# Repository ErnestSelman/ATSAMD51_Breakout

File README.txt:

Notes:
-Board Dimentions: 61.180 mm x 30.365 mm
-Drill sizes were chosen to be one of your free sizes, if any of them is not exactly one of the free sizes then it can be changed to nearest free size.
-PTH Holes sizes are finish hole sizes.

-Drill files:
	-drill_npth.xln
	-dril_pth.xln
-Gerber files included:
	-copper_bottom.gbr
	-copper_top.gbr
	-profile.gbr
	-silkscreen_top.gbr
	-soldermask_bottom.gbr
	-soldermask_top.gbr
-Aditional Files:
	-gerber_job.gbrjob
	-README.txt
	-SAMD51_Breakout.brd
	-SAMD51_Breakout.sch

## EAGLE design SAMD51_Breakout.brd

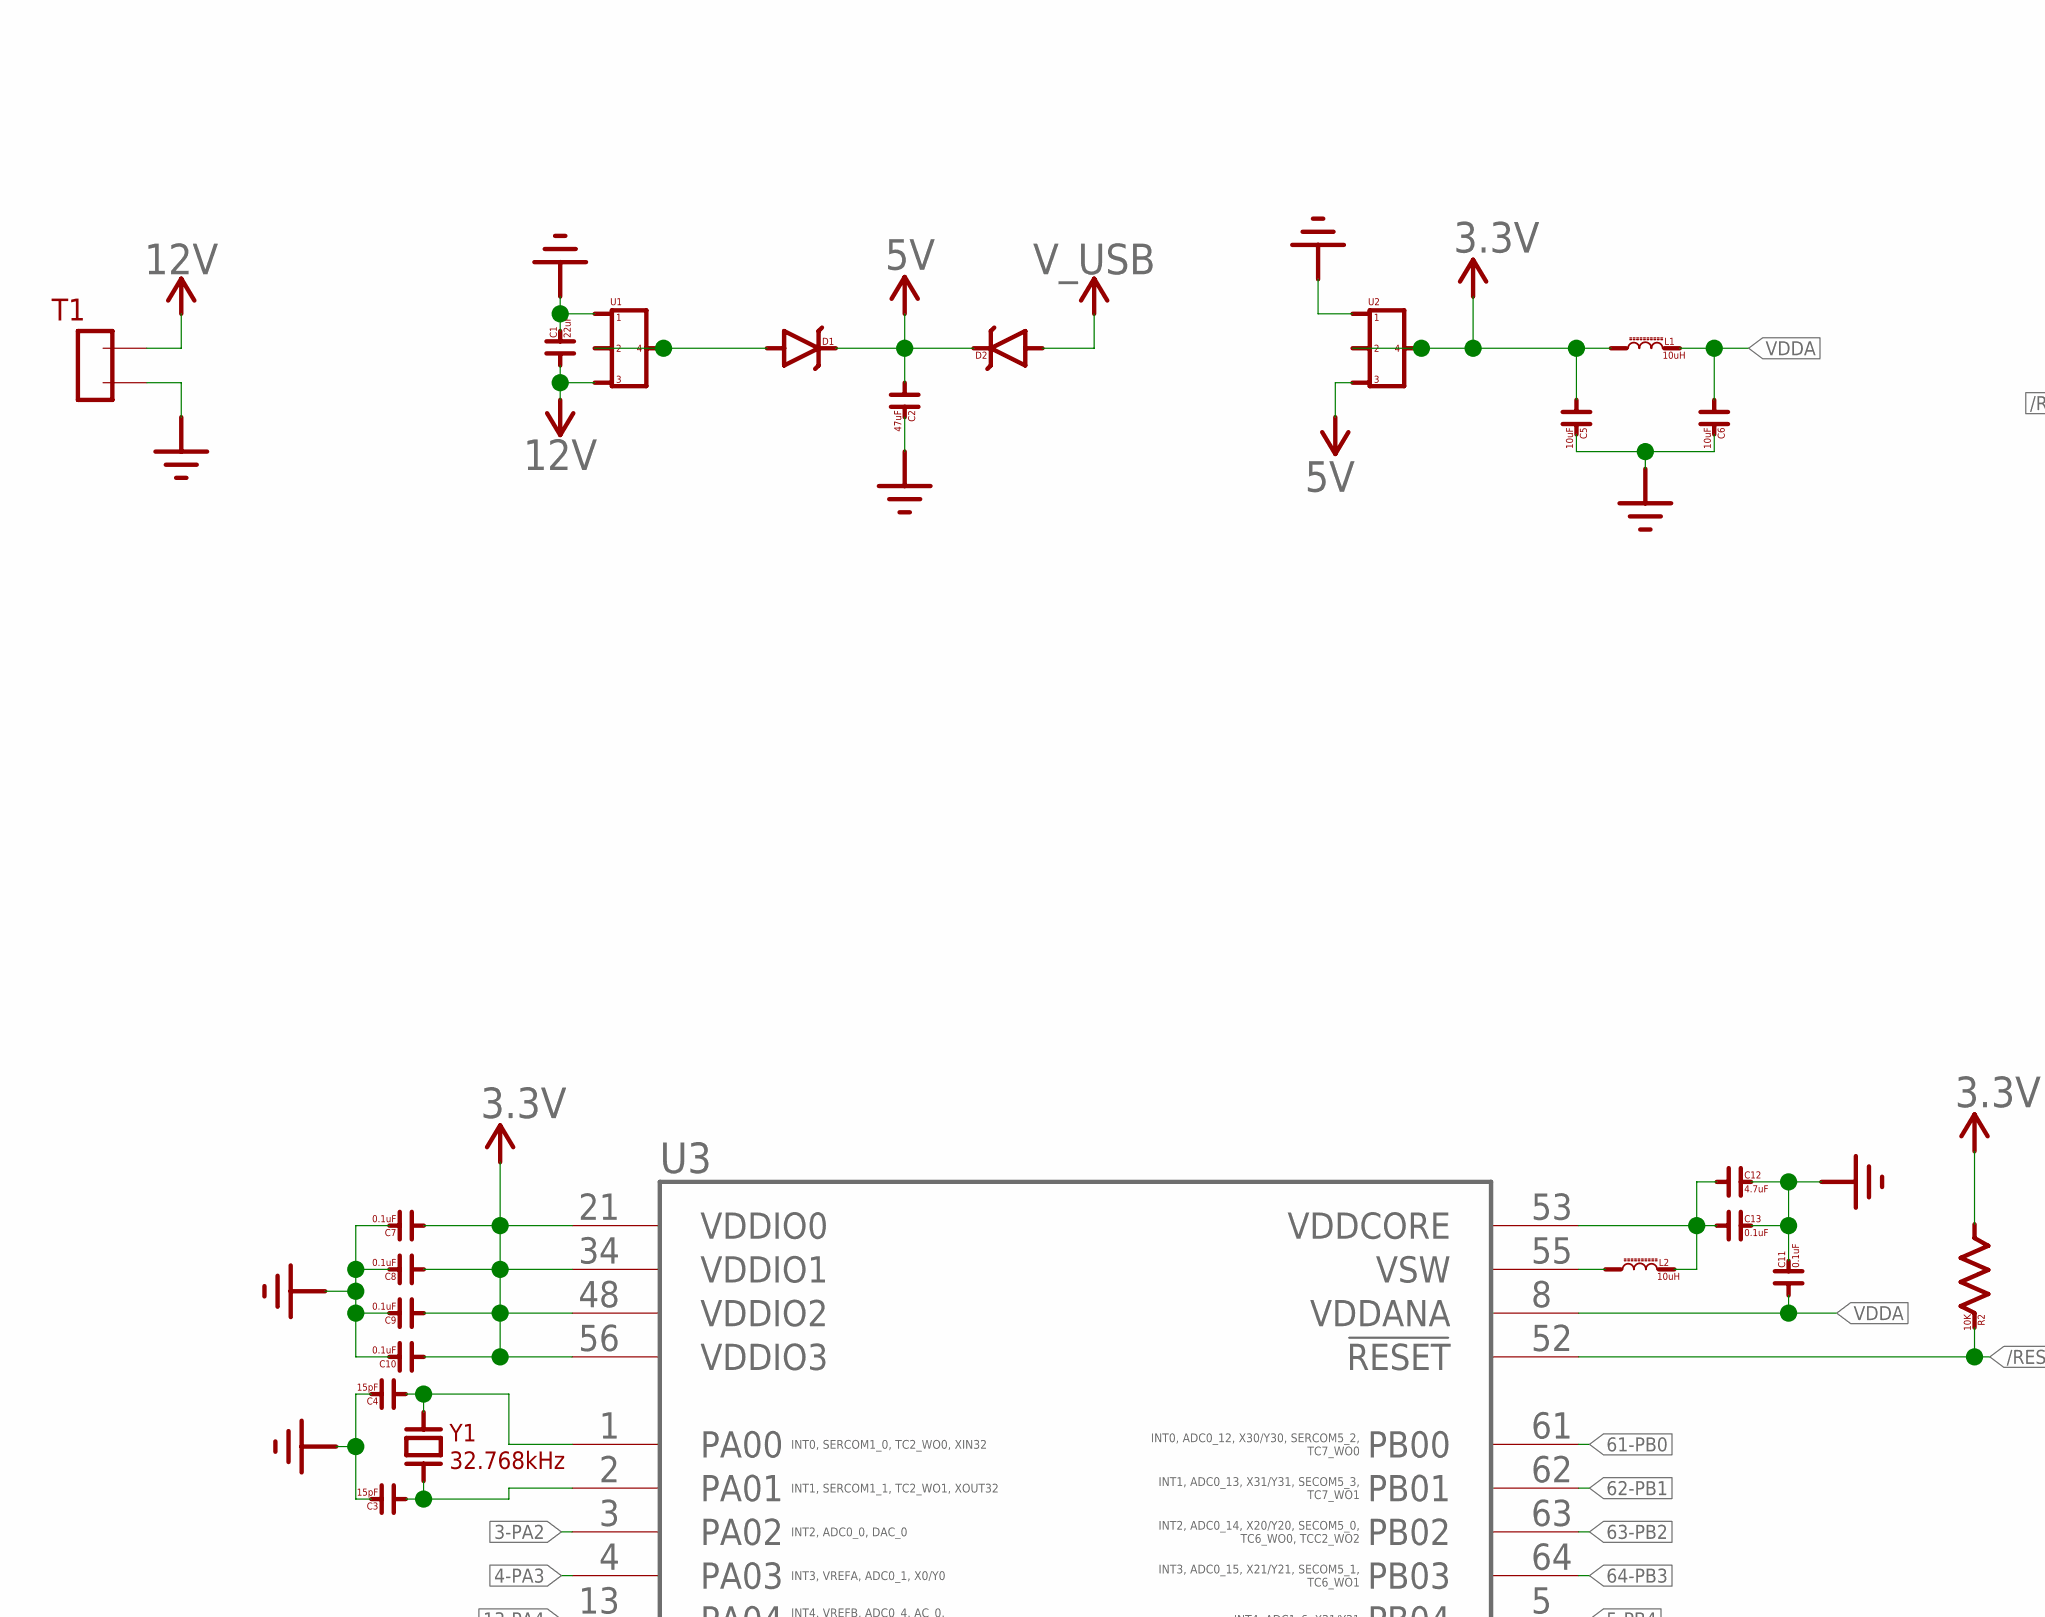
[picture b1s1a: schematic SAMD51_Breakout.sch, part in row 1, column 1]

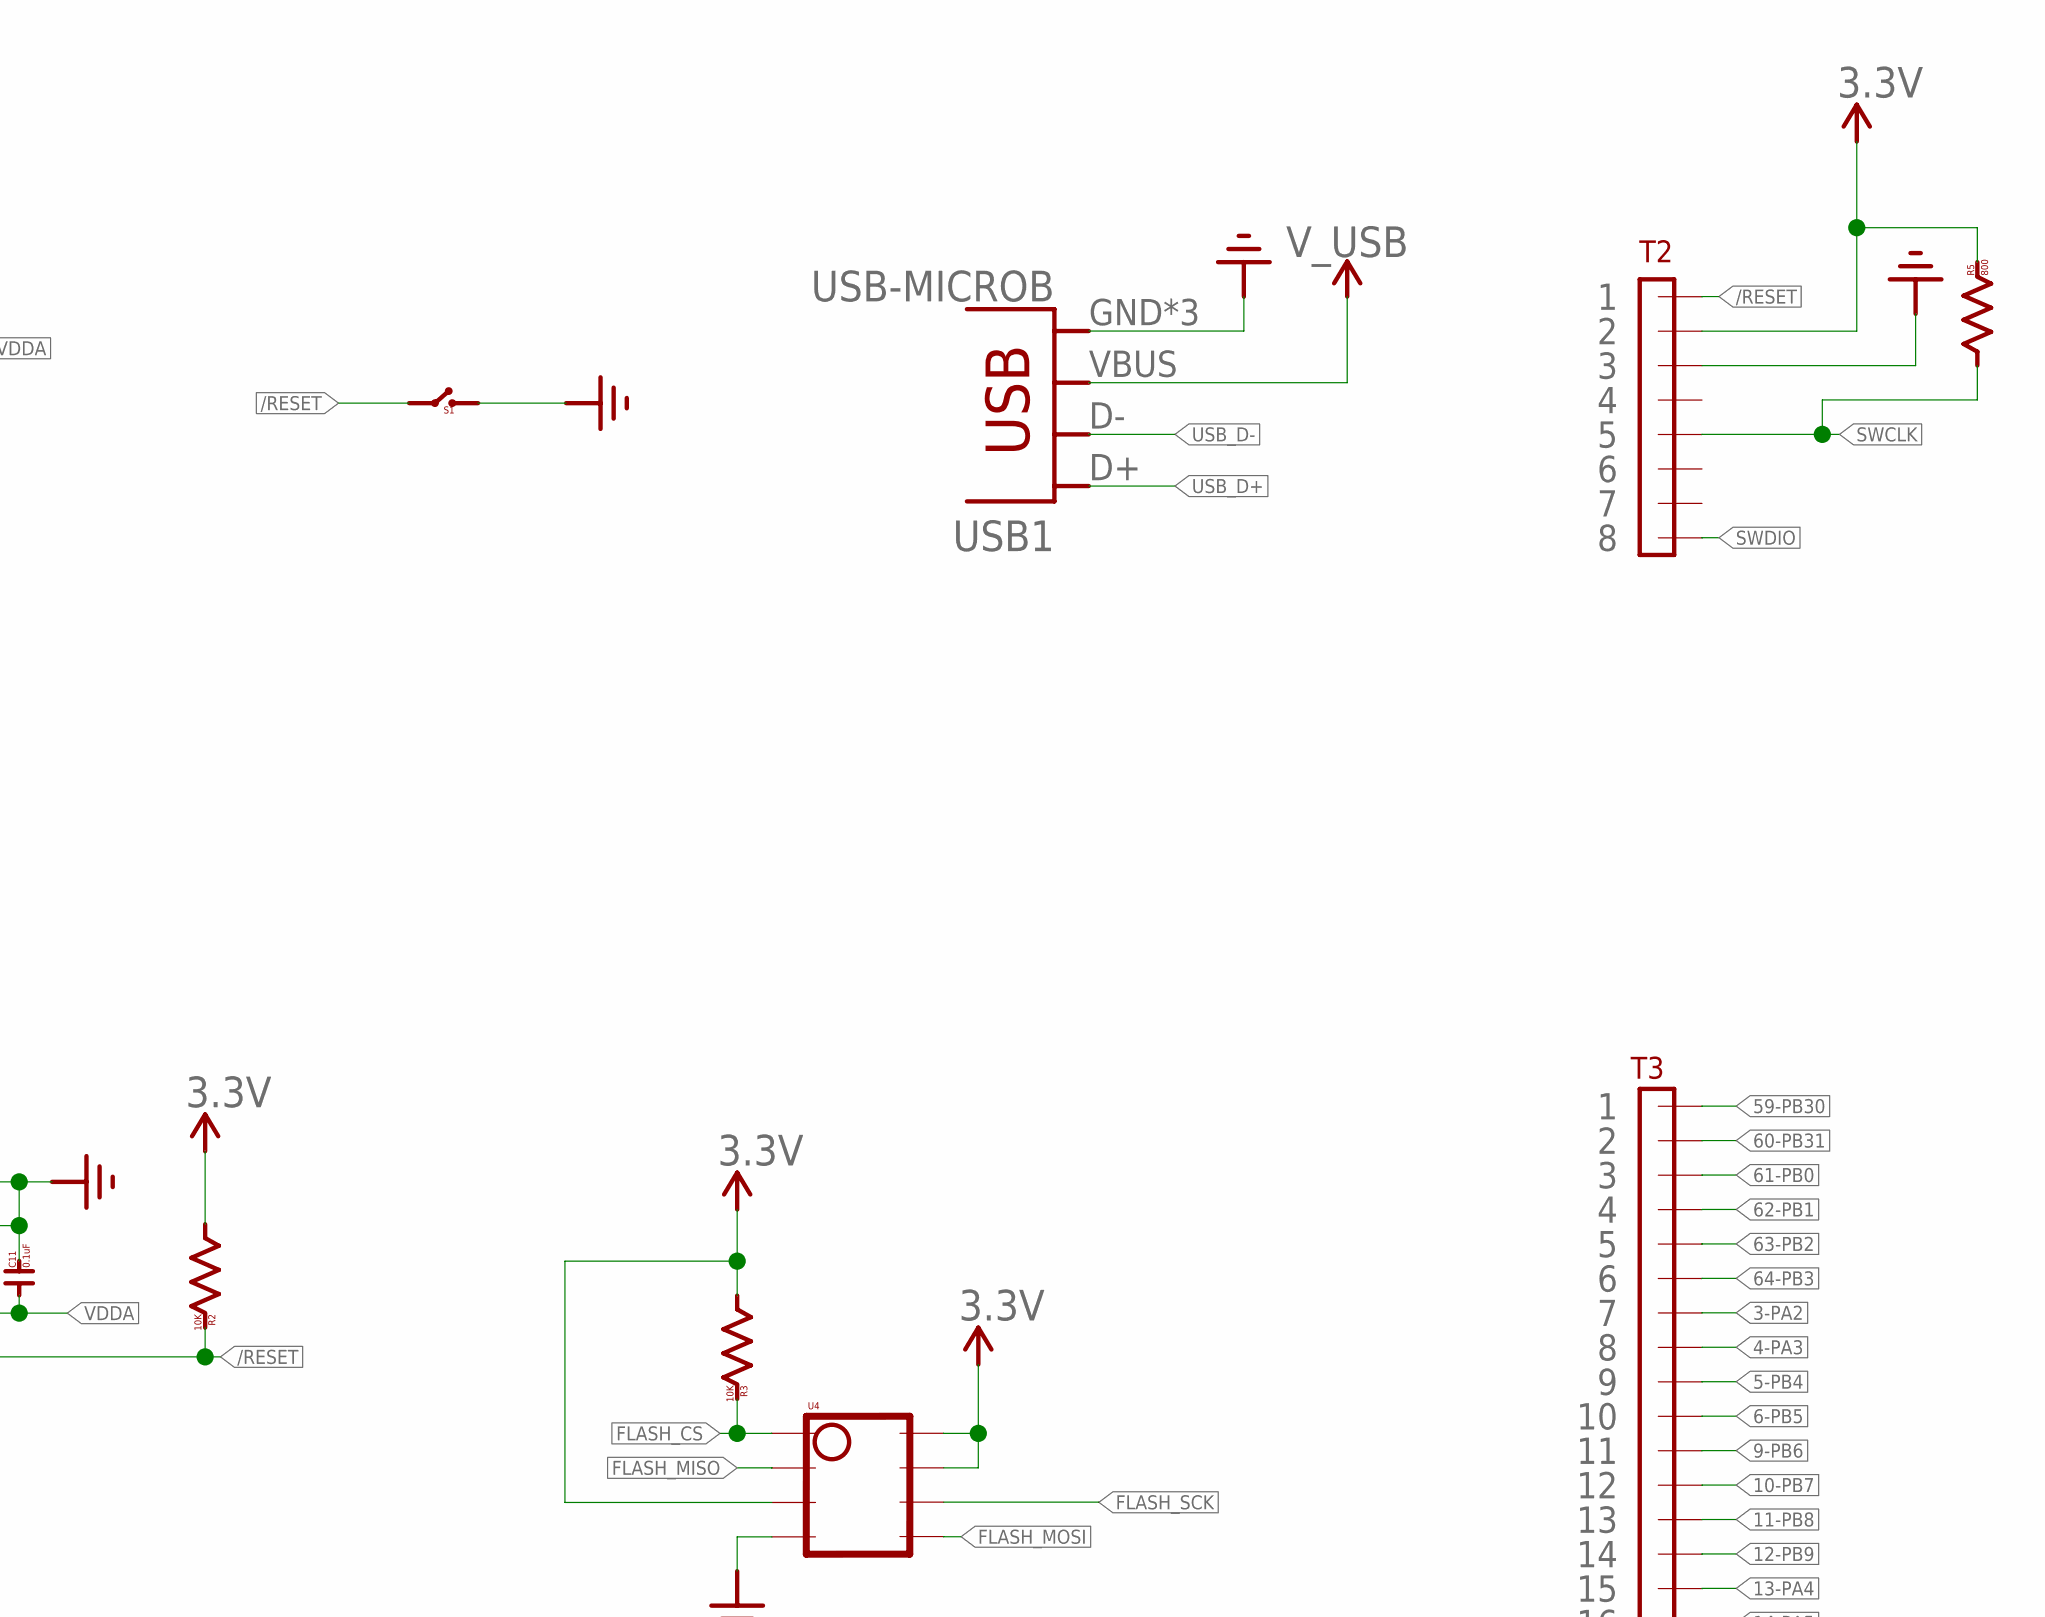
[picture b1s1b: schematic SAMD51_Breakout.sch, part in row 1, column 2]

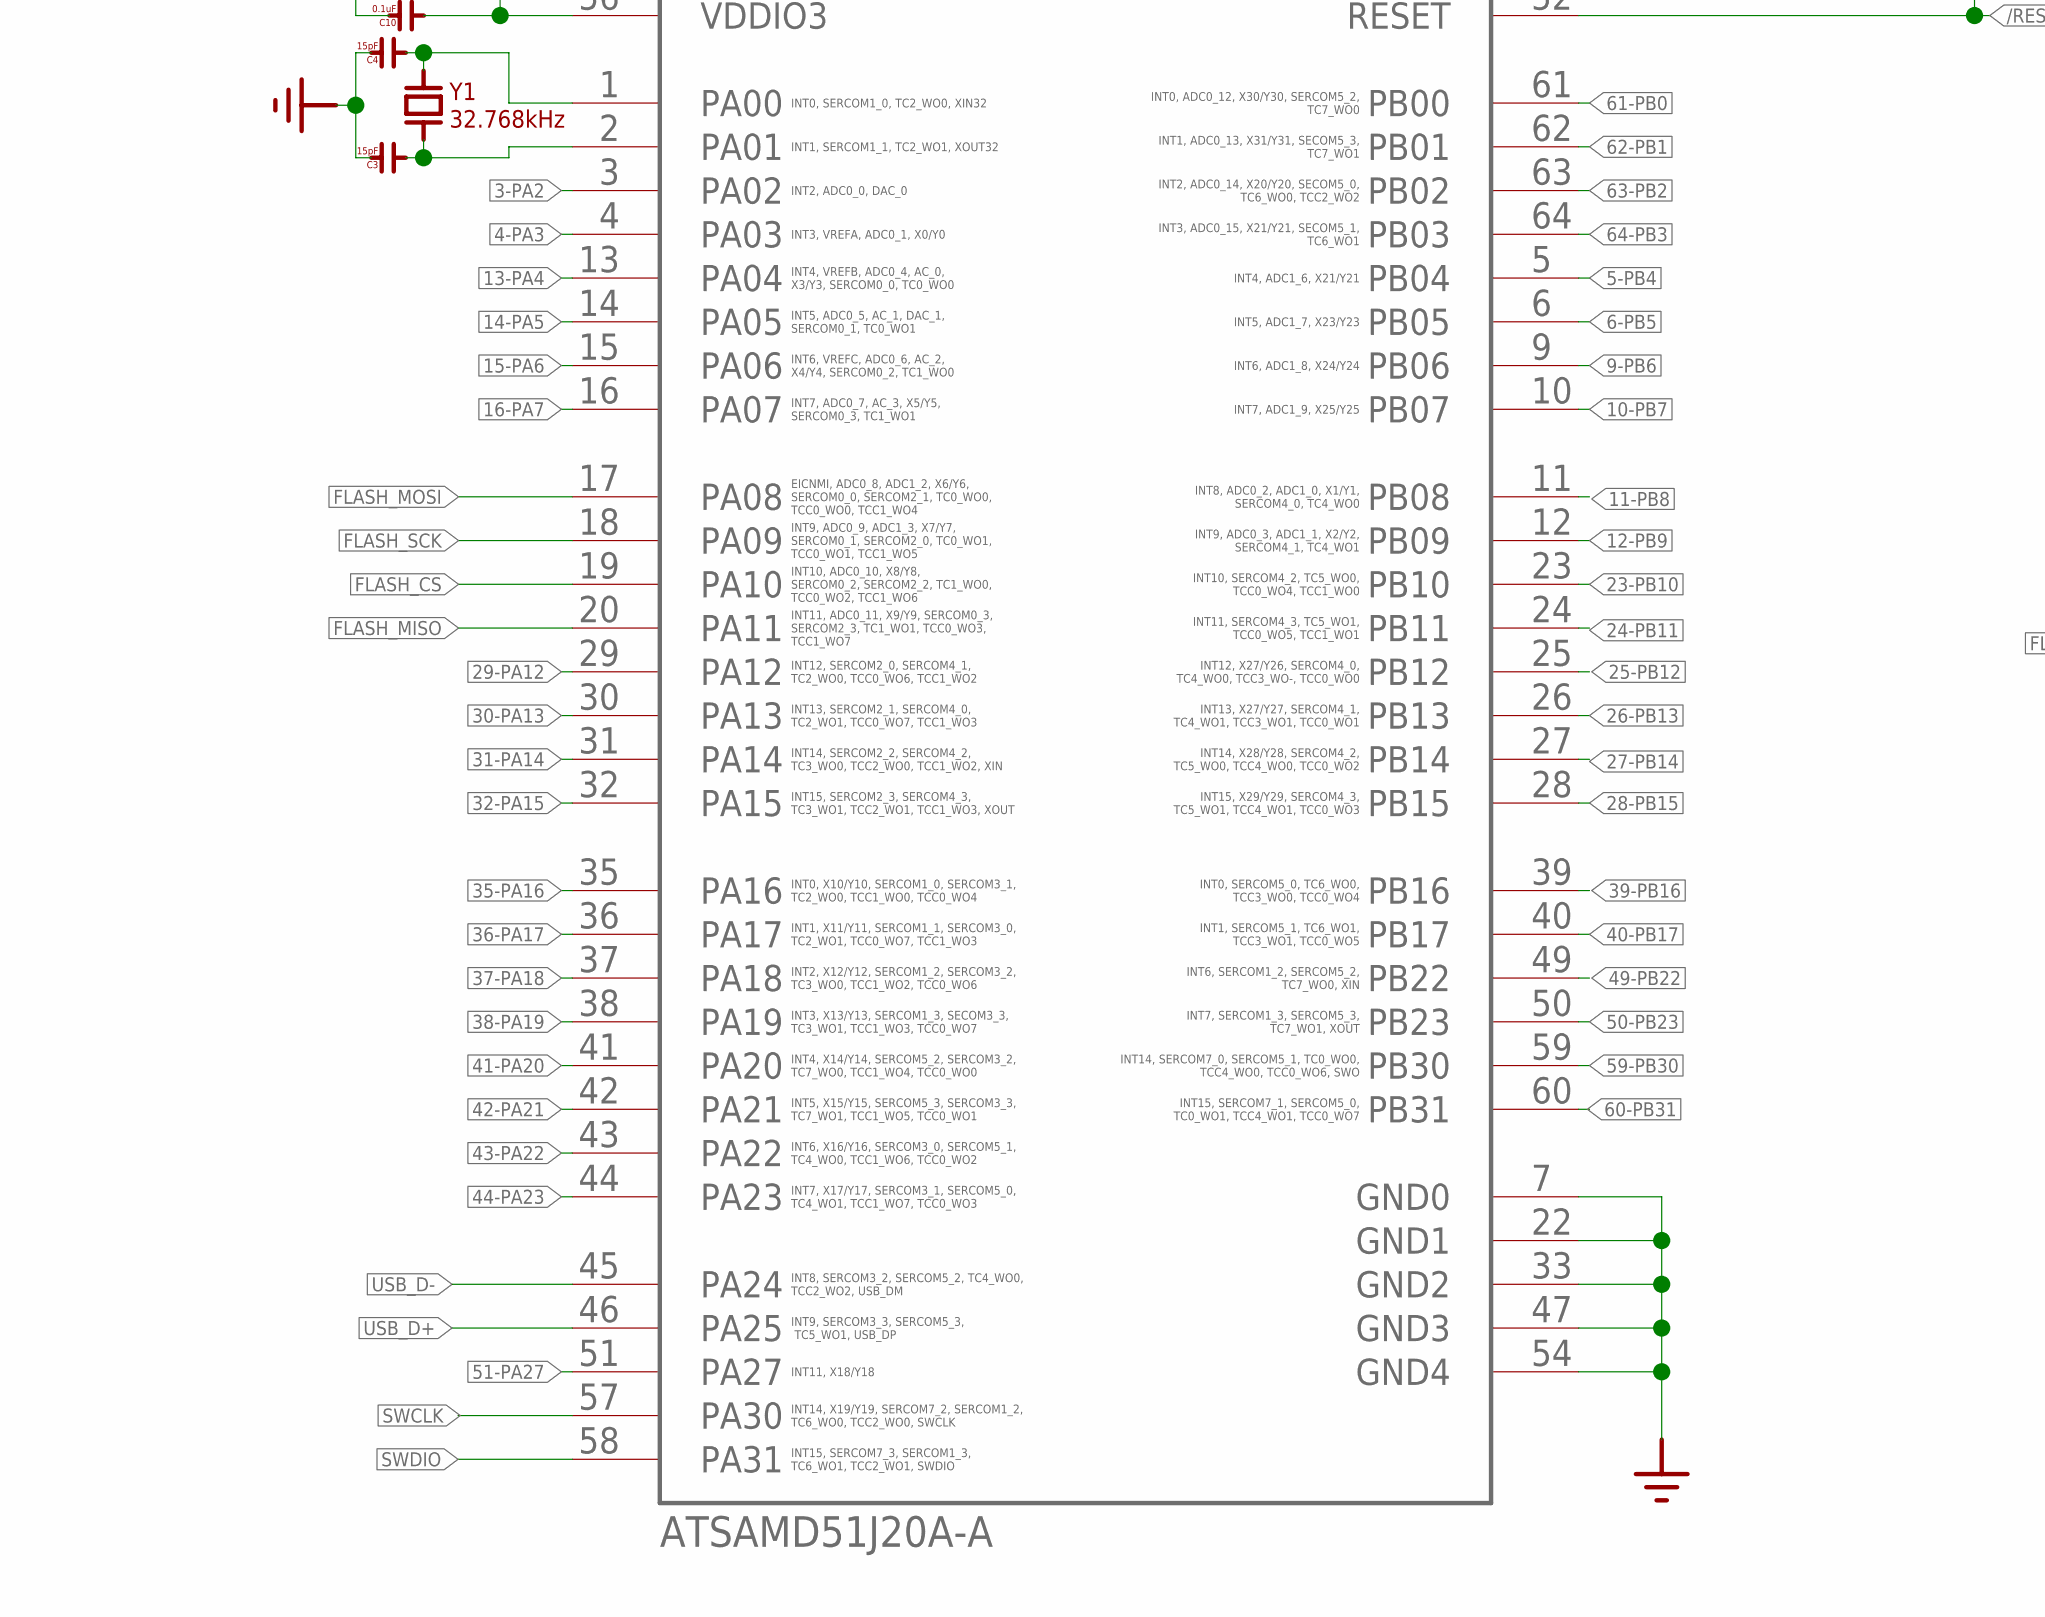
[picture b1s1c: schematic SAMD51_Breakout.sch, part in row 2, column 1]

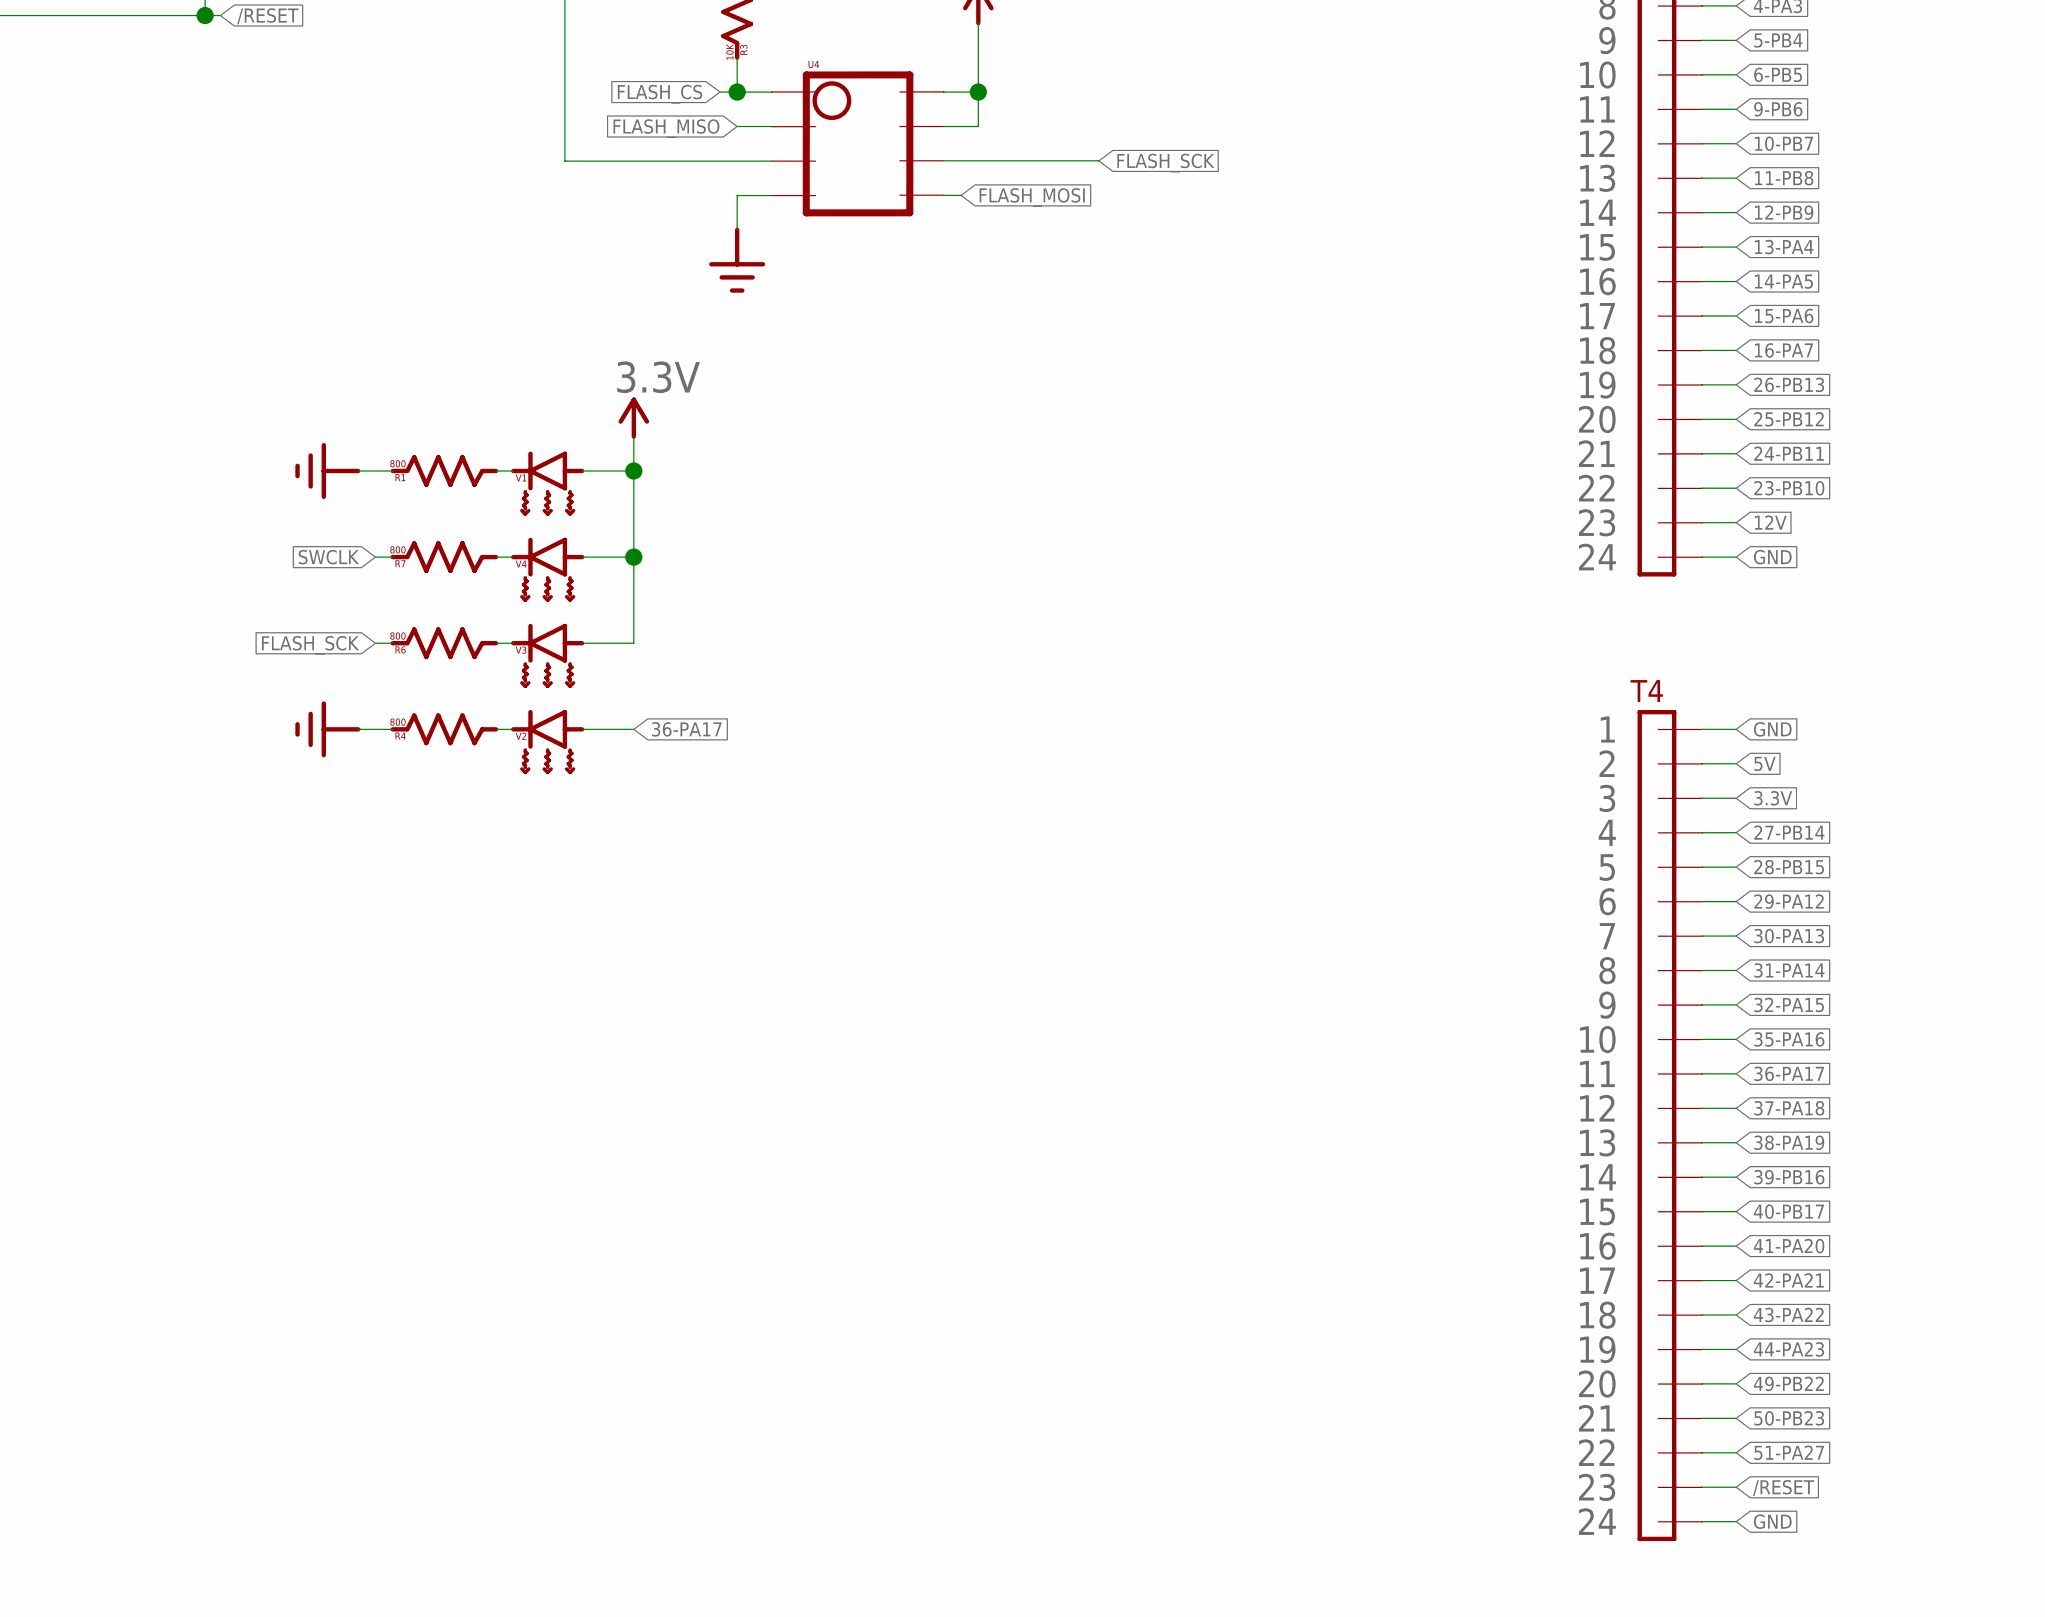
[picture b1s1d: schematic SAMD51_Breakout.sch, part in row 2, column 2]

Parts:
C1: 22uF; 0805
C2: 47uF; 0805
C3, C4: 15pF; 0402
C5, C6: 10uF; 0805
C7, C8, C9, C10, C11, C13: 0.1uF; 0603
C12: 4.7uF; 0603
D1, D2: 1N5819_SMD
L1, L2: 10uH; 0805
R1, R4, R5, R6, R7: 800; 0805
R2, R3: 10K; 0805
S1: SWITCHPTS647; PTS647SK38SMTR2LFS
T1: PHEONIX_1844210
T2: 1X08_90DEG
T3, T4: 1X24
U1, U2: STANDARD_SOT223; SOT223
U3: ATSAMD51J20A-A; TQFP64
U4: SOIC8
USB1: USB-MICROB
V1, V2, V3, V4: LED_0603
Y1: 32.768kHz; CM7V-T1A

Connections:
3-PA2: T3.7, U3.3 (PA02)
3.3V: C5.1, C7.1, C8.1, C9.1, C10.1, L1.1, R2.1, R3.1, R5.2, T2.2, T4.3, U2.2, U2.4, U3.21 (VDDIO0), U3.34 (VDDIO1), U3.48 (VDDIO2), U3.56 (VDDIO3), U4.3, U4.7, U4.8, V1.1, V3.1, V4.1
4-PA3: T3.8, U3.4 (PA03)
5-PB4: T3.9, U3.5 (PB04)
5V: C2.1, D1.P$2, D2.P$2, T4.2, U2.3
6-PB5: T3.10, U3.6 (PB05)
9-PB6: T3.11, U3.9 (PB06)
10-PB7: T3.12, U3.10 (PB07)
11-PB8: T3.13, U3.11 (PB08)
12-PB9: T3.14, U3.12 (PB09)
12V: C1.1, T1.1, T3.23, U1.3
13-PA4: T3.15, U3.13 (PA04)
14-PA5: T3.16, U3.14 (PA05)
15-PA6: T3.17, U3.15 (PA06)
16-PA7: T3.18, U3.16 (PA07)
23-PB10: T3.22, U3.23 (PB10)
24-PB11: T3.21, U3.24 (PB11)
25-PB12: T3.20, U3.25 (PB12)
26-PB13: T3.19, U3.26 (PB13)
27-PB14: T4.4, U3.27 (PB14)
28-PB15: T4.5, U3.28 (PB15)
29-PA12: T4.6, U3.29 (PA12)
30-PA13: T4.7, U3.30 (PA13)
31-PA14: T4.8, U3.31 (PA14)
32-PA15: T4.9, U3.32 (PA15)
35-PA16: T4.10, U3.35 (PA16)
36-PA17: T4.11, U3.36 (PA17), V2.1
37-PA18: T4.12, U3.37 (PA18)
38-PA19: T4.13, U3.38 (PA19)
39-PB16: T4.14, U3.39 (PB16)
40-PB17: T4.15, U3.40 (PB17)
41-PA20: T4.16, U3.41 (PA20)
42-PA21: T4.17, U3.42 (PA21)
43-PA22: T4.18, U3.43 (PA22)
44-PA23: T4.19, U3.44 (PA23)
49-PB22: T4.20, U3.49 (PB22)
50-PB23: T4.21, U3.50 (PB23)
51-PA27: T4.22, U3.51 (PA27)
59-PB30: T3.1, U3.59 (PB30)
60-PB31: T3.2, U3.60 (PB31)
61-PB0: T3.3, U3.61 (PB00)
62-PB1: T3.4, U3.62 (PB01)
63-PB2: T3.5, U3.63 (PB02)
64-PB3: T3.6, U3.64 (PB03)
/RESET: R2.2, S1.P$1, S1.P$2, T2.1, T4.23, U3.52 (!RESET)
FLASH_CS: R3.2, U3.19 (PA10), U4.1
FLASH_MISO: U3.20 (PA11), U4.2
FLASH_MOSI: U3.17 (PA08), U4.5
FLASH_SCK: R6.2, U3.18 (PA09), U4.6
GND: C1.2, C2.2, C3.2, C4.2, C5.2, C6.2, C7.2, C8.2, C9.2, C10.2, C11.2, C12.2, C13.2, R1.2, R4.2, S1.P$3, S1.P$4, T1.2, T2.3, T3.24, T4.1, T4.24, U1.1, U2.1, U3.7 (GND0), U3.22 (GND1), U3.33 (GND2), U3.47 (GND3), U3.54 (GND4), U4.4, USB1.GND, USB1.MT1 (GND), USB1.MT2 (GND)
unnamed: R1.1, V1.2
unnamed: R4.1, V2.2
unnamed: C4.1, U3.1 (PA00), Y1.P$2
unnamed: D1.P$1, U1.2, U1.4
unnamed: C3.1, U3.2 (PA01), Y1.P$1
unnamed: R6.1, V3.2
unnamed: R7.1, V4.2
SWCLK: R5.1, R7.2, T2.5, U3.57 (PA30)
SWDIO: T2.8, U3.58 (PA31)
USB_D+: U3.46 (PA25), USB1.D+
USB_D-: U3.45 (PA24), USB1.D-
VDDA: C6.1, C11.1, L1.2, U3.8 (VDDANA)
VDDCORE: C12.1, C13.1, L2.2, U3.53 (VDDCORE)
VSW: L2.1, U3.55 (VSW)
V_USB: D2.P$1, USB1.VBUS

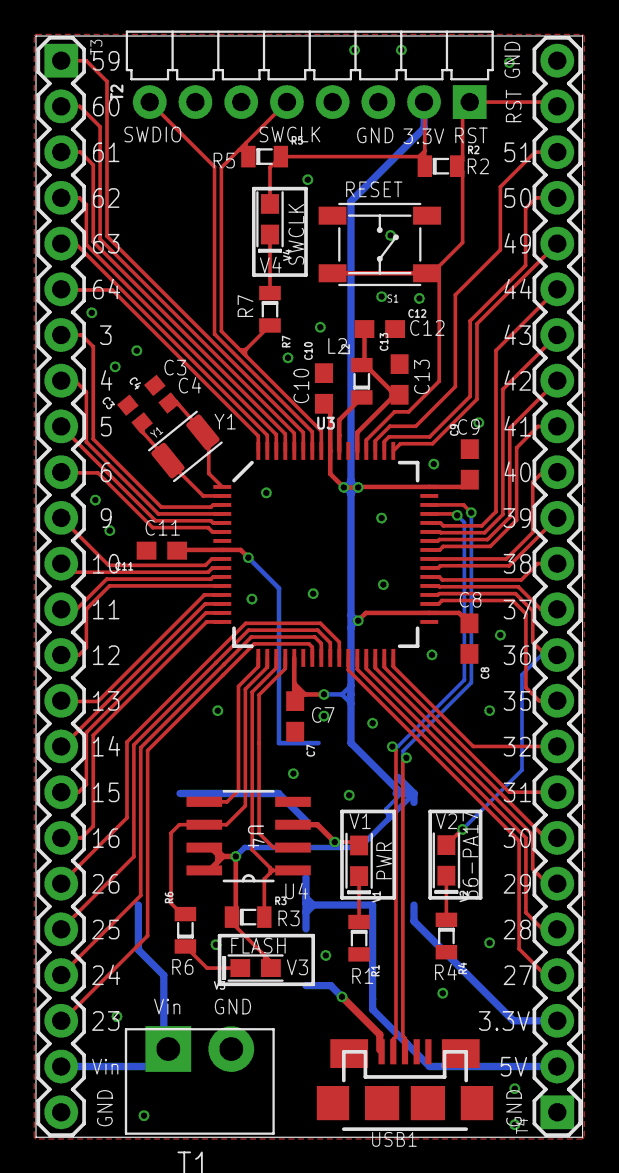
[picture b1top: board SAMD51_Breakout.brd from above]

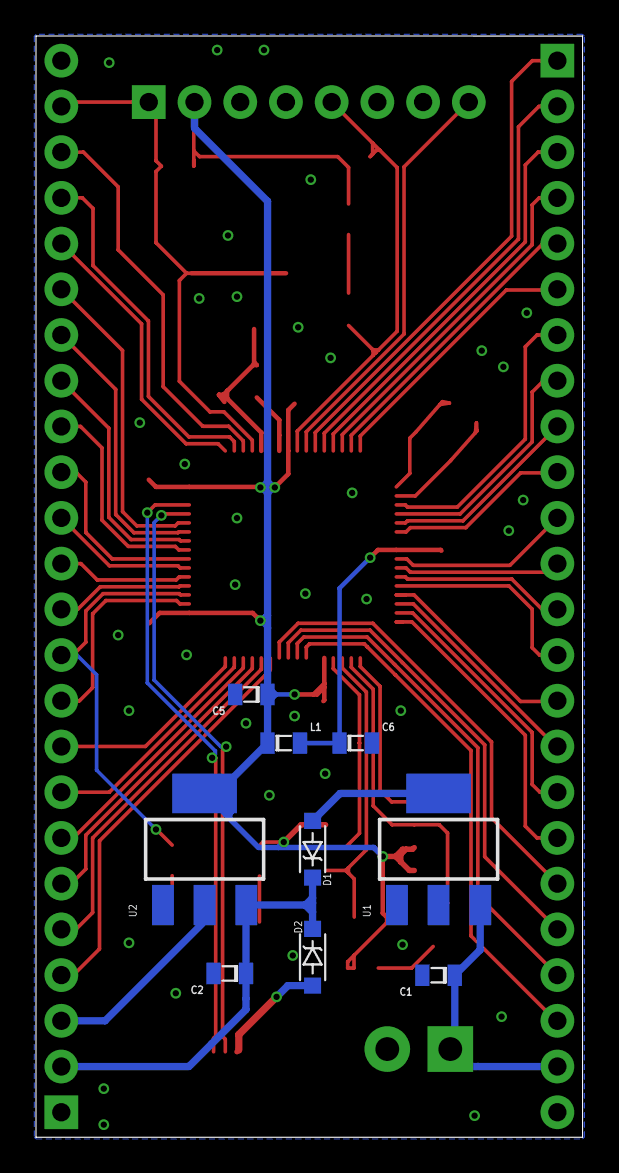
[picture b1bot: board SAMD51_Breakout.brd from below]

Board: 2 copper layers, 30.4 x 61.2 mm, 39 parts (9 on the bottom side), 65 nets.

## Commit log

2020-05-07 First commit, bringing all files into repo. Project was already done
2020-05-07 Fixing README and INFO. Adding BoM

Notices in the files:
parts and their libraries:
SparkFun-IC-Microcontroller: Licensing: Creative Commons ShareAlike 4.0 International - https://creativecommons.org/licenses/by-sa/4.0
